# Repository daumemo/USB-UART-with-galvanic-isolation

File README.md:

# USB-UART-with-galvanic-isolation

A DIY USB-UART adapter for working with devices which need such isolation. Great for programming for e.g. power meter which does not have any isolation from mains voltage. Mainly used for ESP8266 programming, but can be used for any device with UART interface.

You can read more about it:
https://daumemo.com/diy-galvanically-isolated-usb-uart-adapter/

Thing: https://www.thingiverse.com/thing:3703276

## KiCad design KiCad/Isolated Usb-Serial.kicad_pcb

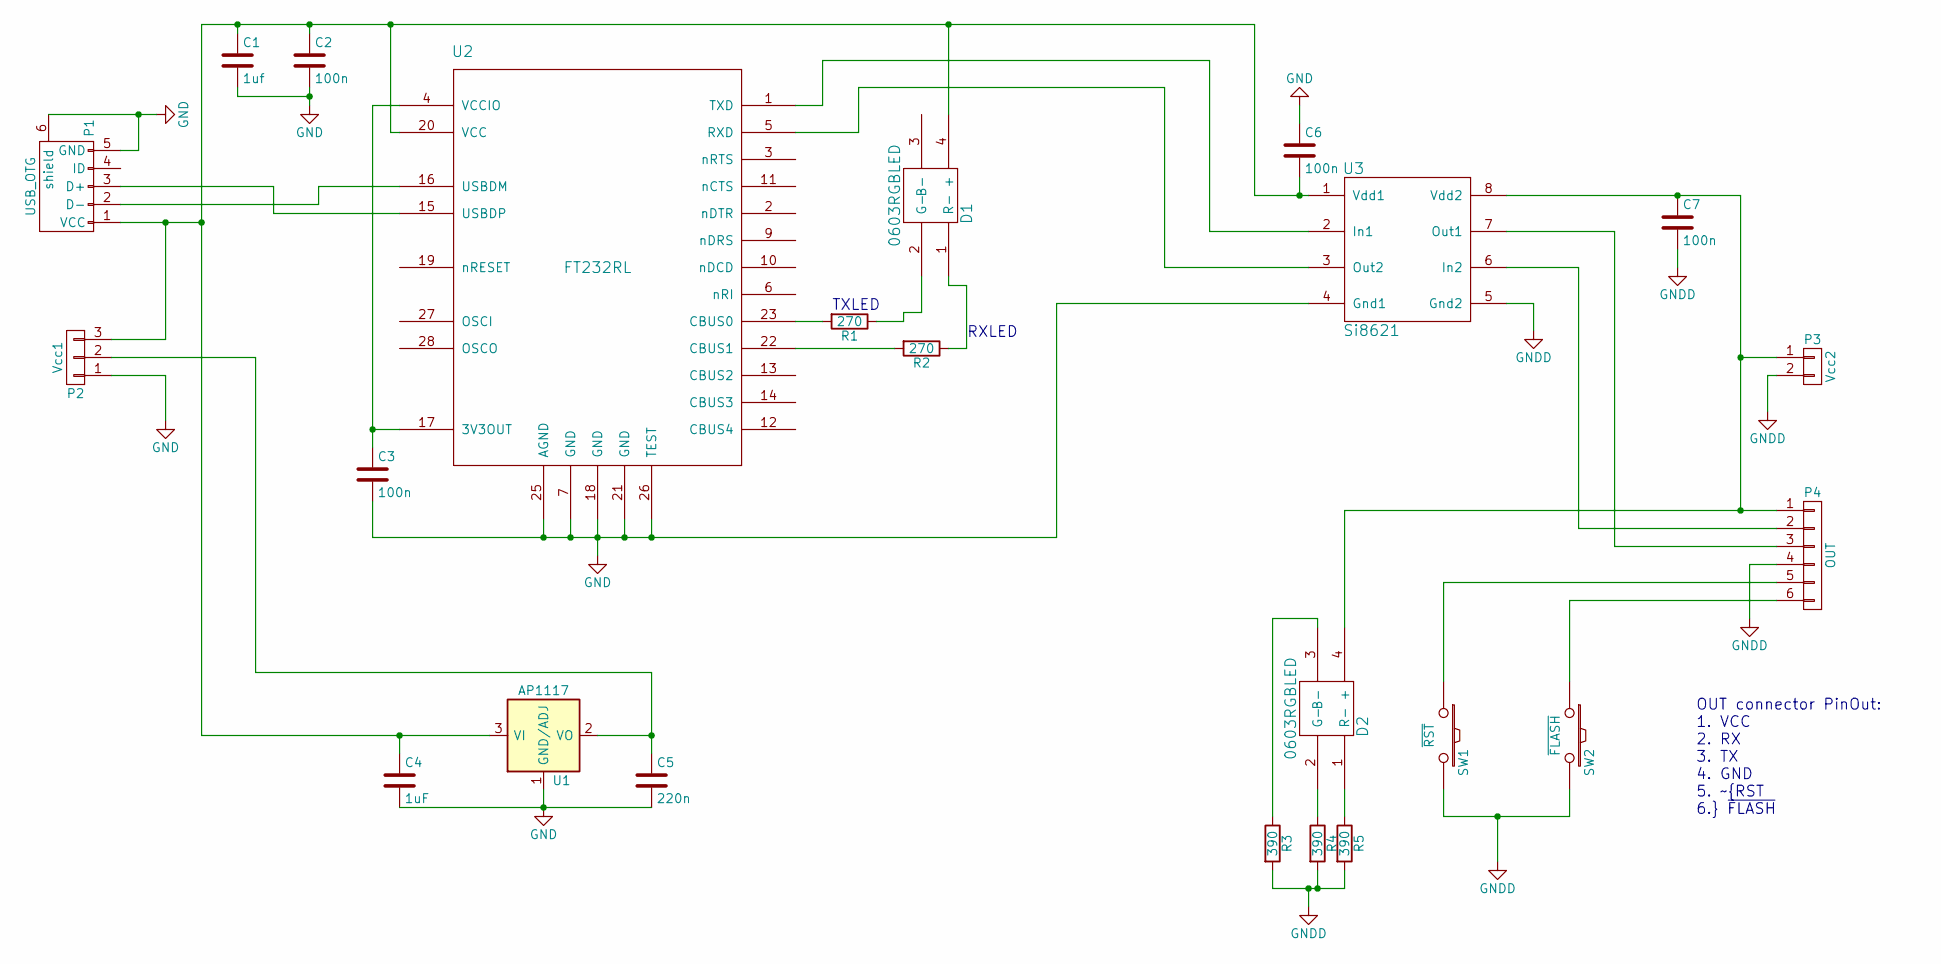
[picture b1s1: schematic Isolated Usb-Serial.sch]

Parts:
C1: 1uf; C_0603
C2, C3, C6, C7: 100n; C_0603
C4: 1uF; C_0603
C5: 220n; C_0603
D1, D2: 0603RGBLED; 0603_rgb_led
P1: USB_OTG; USB_Mini-B
P2: Vcc1; Pin_Header_Straight_1x03
P3: Vcc2; Pin_Header_Straight_1x02
P4: OUT; Pin_Header_Angled_1x06
R1, R2: 270; R_0603
R3, R4, R5: 390; R_0603
SW1: ~RST; SW_SPST_EVQP0
SW2: ~FLASH; SW_SPST_EVQP0
U1: AP1117; SOT-223
U2: FT232RL; SSOP28
U3: Si8621; SOIC-8-N

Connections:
GND: C1.2, C2.2, C3.2, C4.2, C5.2, C6.1, P1.5 (GND), P1.6 (shield), P2.1, U1.1 (GND/ADJ), U2.7 (GND), U2.18 (GND), U2.21 (GND), U2.25 (AGND), U2.26 (TEST), U3.4 (Gnd1)
GNDD: C7.2, P3.2, P4.4, R3.2, R4.2, R5.2, SW1.2, SW2.2, U3.5 (Gnd2)
unnamed: C1.1, C2.1, C4.1, C6.2, D1.4 (+), P1.1 (VCC), P2.3, U1.3 (VI), U2.20 (VCC), U3.1 (Vdd1)
unnamed: C3.1, U2.4 (VCCIO), U2.17 (3V3OUT)
unnamed: C5.1, P2.2, U1.2 (VO)
unnamed: C7.1, D2.4 (+), P3.1, P4.1, U3.8 (Vdd2)
unnamed: D1.1 (R-), R2.1
unnamed: D1.2 (G-), R1.1
unnamed: D2.1 (R-), R5.1
unnamed: D2.2 (G-), R4.1
unnamed: D2.3 (B-), R3.1
unnamed: P1.2 (D-), U2.16 (USBDM)
unnamed: P1.3 (D+), U2.15 (USBDP)
unnamed: P4.2, U3.6 (In2)
unnamed: P4.3, U3.7 (Out1)
unnamed: P4.5, SW1.1
unnamed: P4.6, SW2.1
unnamed: R1.2, U2.23 (CBUS0)
unnamed: R2.2, U2.22 (CBUS1)
unnamed: U2.1 (TXD), U3.2 (In1)
unnamed: U2.5 (RXD), U3.3 (Out2)

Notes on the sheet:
TXLED
RXLED
OUT connector PinOut: 1. VCC 2. RX 3. TX 4. GND 5. ~RST 6. ~FLASH

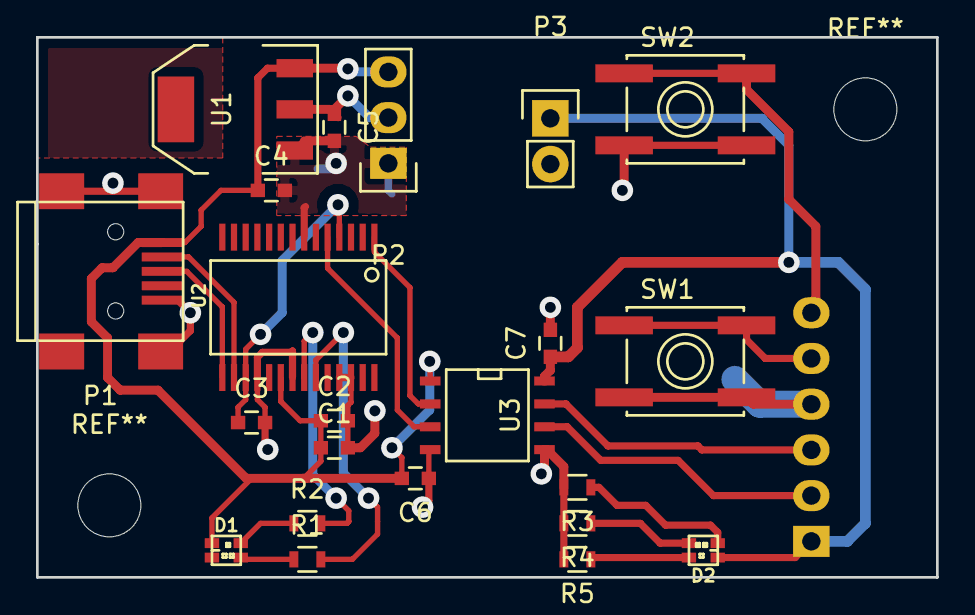
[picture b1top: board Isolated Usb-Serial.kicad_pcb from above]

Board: 2 copper layers, 50.0 x 30.0 mm, 23 parts (1 on the bottom side), 21 nets.
